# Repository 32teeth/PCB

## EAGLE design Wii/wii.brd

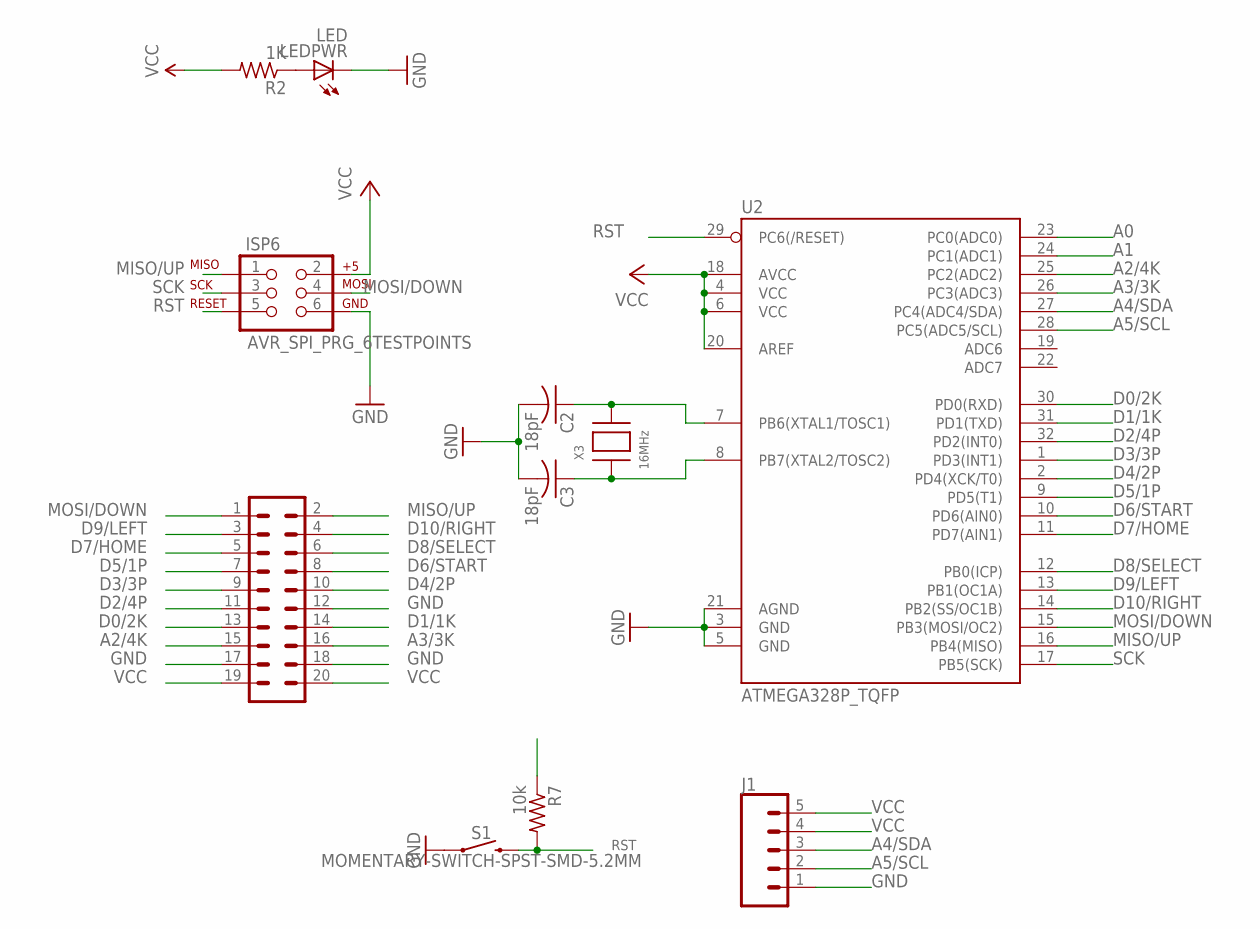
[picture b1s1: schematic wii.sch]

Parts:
C2, C3: 18pF; C0805
ISP6: AVR_SPI_PRG_6TESTPOINTS; 2X3_TEST_POINTS
J1: CONN_05; 1X05
LEDPWR: LED; CHIPLED_0805
R2: 1K; R0805
R7: 10k; R0805
S1: MOMENTARY-SWITCH-SPST-SMD-5.2MM; TACTILE_SWITCH_SMD_5.2MM
U2: ATMEGA328P_TQFP; TQFP32-08
U$1: 20 pin breakout; 2X10_ROUND_NOSILK
X3: 16MHz; NX5032

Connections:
A0: U2.23 (PC0(ADC0))
A1: U2.24 (PC1(ADC1))
A2/4K: U2.25 (PC2(ADC2)), U$1.15
A3/3K: U2.26 (PC3(ADC3)), U$1.16
A4/SDA: J1.3, U2.27 (PC4(ADC4/SDA))
A5/SCL: J1.2, U2.28 (PC5(ADC5/SCL))
D0/2K: U2.30 (PD0(RXD)), U$1.13
D1/1K: U2.31 (PD1(TXD)), U$1.14
D2/4P: U2.32 (PD2(INT0)), U$1.11
D3/3P: U2.1 (PD3(INT1)), U$1.9
D4/2P: U2.2 (PD4(XCK/T0)), U$1.10
D5/1P: U2.9 (PD5(T1)), U$1.7
D6/START: U2.10 (PD6(AIN0)), U$1.8
D7/HOME: U2.11 (PD7(AIN1)), U$1.5
D8/SELECT: U2.12 (PB0(ICP)), U$1.6
D9/LEFT: U2.13 (PB1(OC1A)), U$1.3
D10/RIGHT: U2.14 (PB2(SS/OC1B)), U$1.4
GND: C2.2, C3.2, ISP6.6, J1.1, LEDPWR.C, S1.1, U2.3 (GND), U2.5 (GND), U2.21 (AGND), U$1.12, U$1.17, U$1.18
MISO/UP: ISP6.1, U2.16 (PB4(MISO)), U$1.2
MOSI/DOWN: ISP6.4, U2.15 (PB3(MOSI/OC2)), U$1.1
unnamed: LEDPWR.A, R2.1
unnamed: C2.1, U2.7 (PB6(XTAL1/TOSC1)), X3.P$2
unnamed: C3.1, U2.8 (PB7(XTAL2/TOSC2)), X3.P$1
RST: ISP6.5, R7.2, S1.3 (2), U2.29 (PC6(/RESET))
SCK: ISP6.3, U2.17 (PB5(SCK))
VCC: ISP6.2, J1.4, J1.5, R2.2, R7.1, U2.4 (VCC), U2.6 (VCC), U2.18 (AVCC), U2.20 (AREF), U$1.19, U$1.20

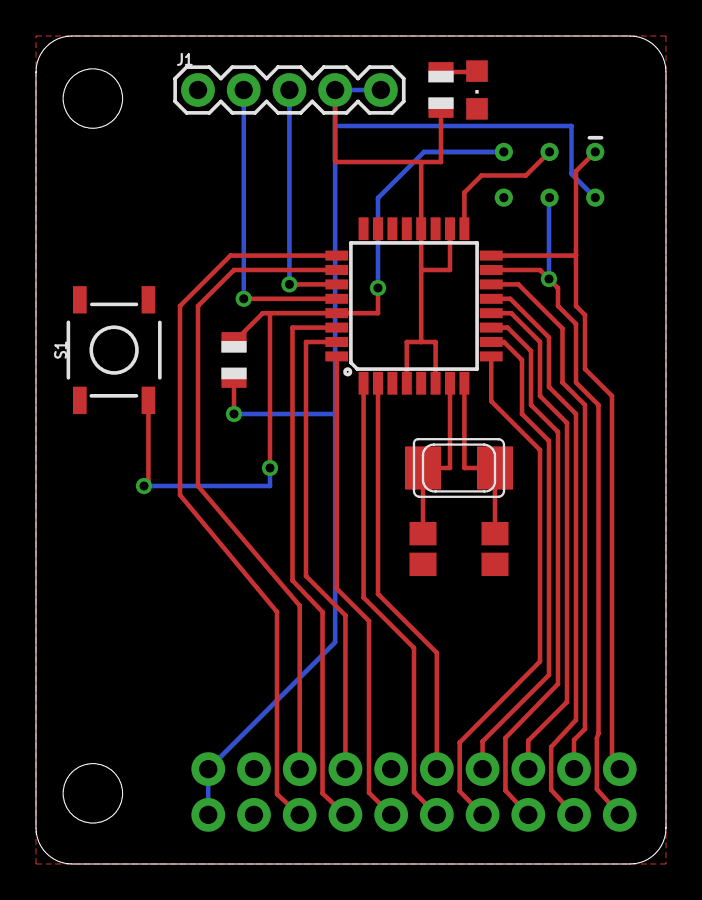
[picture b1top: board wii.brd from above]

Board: 2 copper layers, 35.0 x 46.0 mm, 13 parts (1 on the bottom side), 24 nets.

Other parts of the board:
U$2, U$3: STAND-OFF

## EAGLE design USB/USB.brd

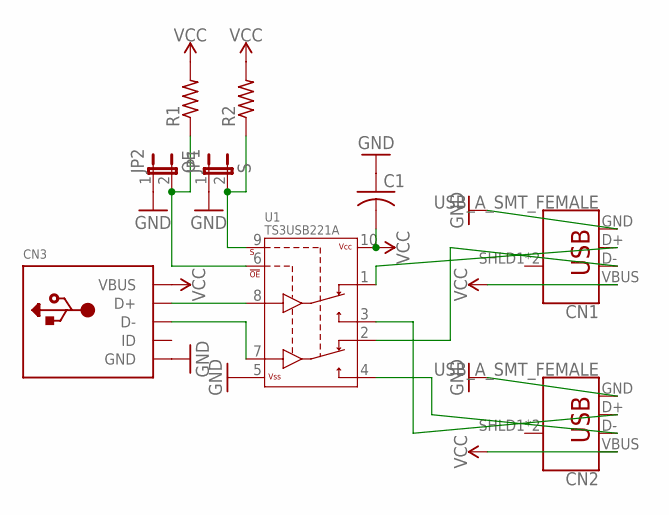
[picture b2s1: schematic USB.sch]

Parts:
C1: C-USC0402K; C0402K
CN1, CN2: USB_A_SMT_FEMALE; USB-A-S-SILK-FEMALE
CN3: USBMINIB; USB-MINIB
JP1: S; 1X02
JP2: OE; 1X02
R1, R2: R-US_R0402; R0402
U1: TS3USB221A; QFN-10-RSE

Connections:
GND: C1.1, CN1.GND, CN2.GND, CN3.GND, JP1.1, JP2.1, U1.5 (VSS)
unnamed: CN3.D+, U1.8 (D+)
unnamed: CN3.D-, U1.7 (D-)
unnamed: CN1.D+, U1.1 (1D+)
unnamed: CN2.D+, U1.3 (2D+)
unnamed: CN1.D-, U1.2 (1D-)
unnamed: CN2.D-, U1.4 (2D-)
unnamed: JP2.2, R1.1, U1.6 (!OE)
unnamed: JP1.2, R2.1, U1.9 (S)
VCC: C1.2, CN1.VBUS, CN2.VBUS, CN3.VBUS, R1.2, R2.2, U1.10 (VCC)

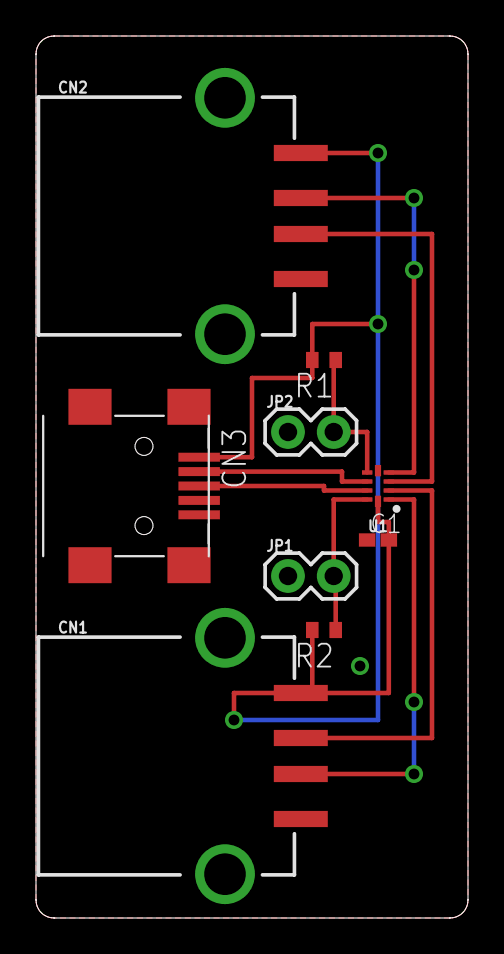
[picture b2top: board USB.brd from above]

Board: 2 copper layers, 24.0 x 49.0 mm, 9 parts (0 on the bottom side), 10 nets.

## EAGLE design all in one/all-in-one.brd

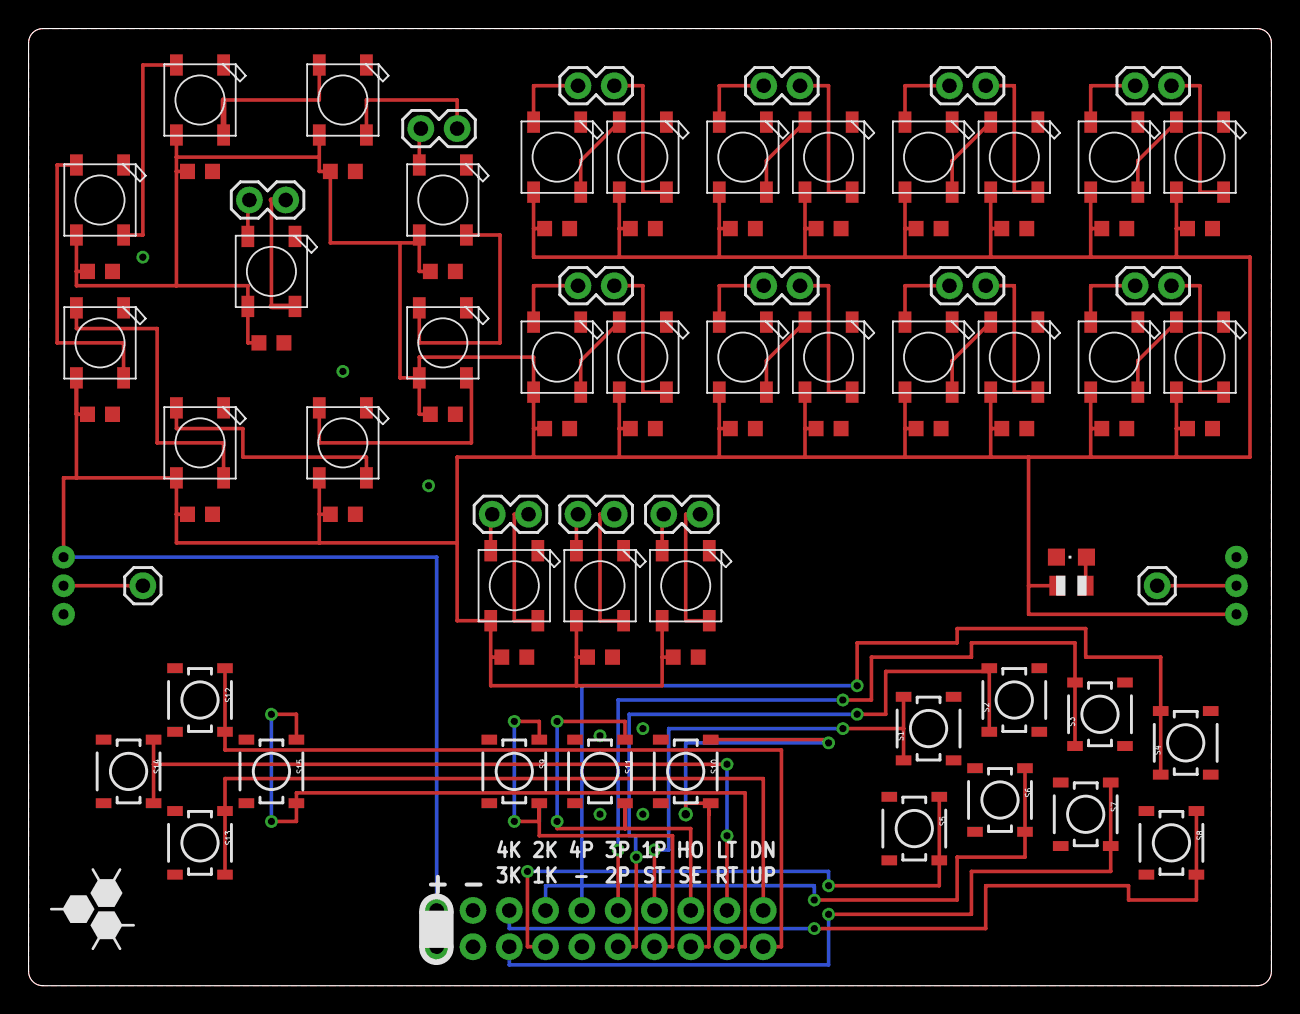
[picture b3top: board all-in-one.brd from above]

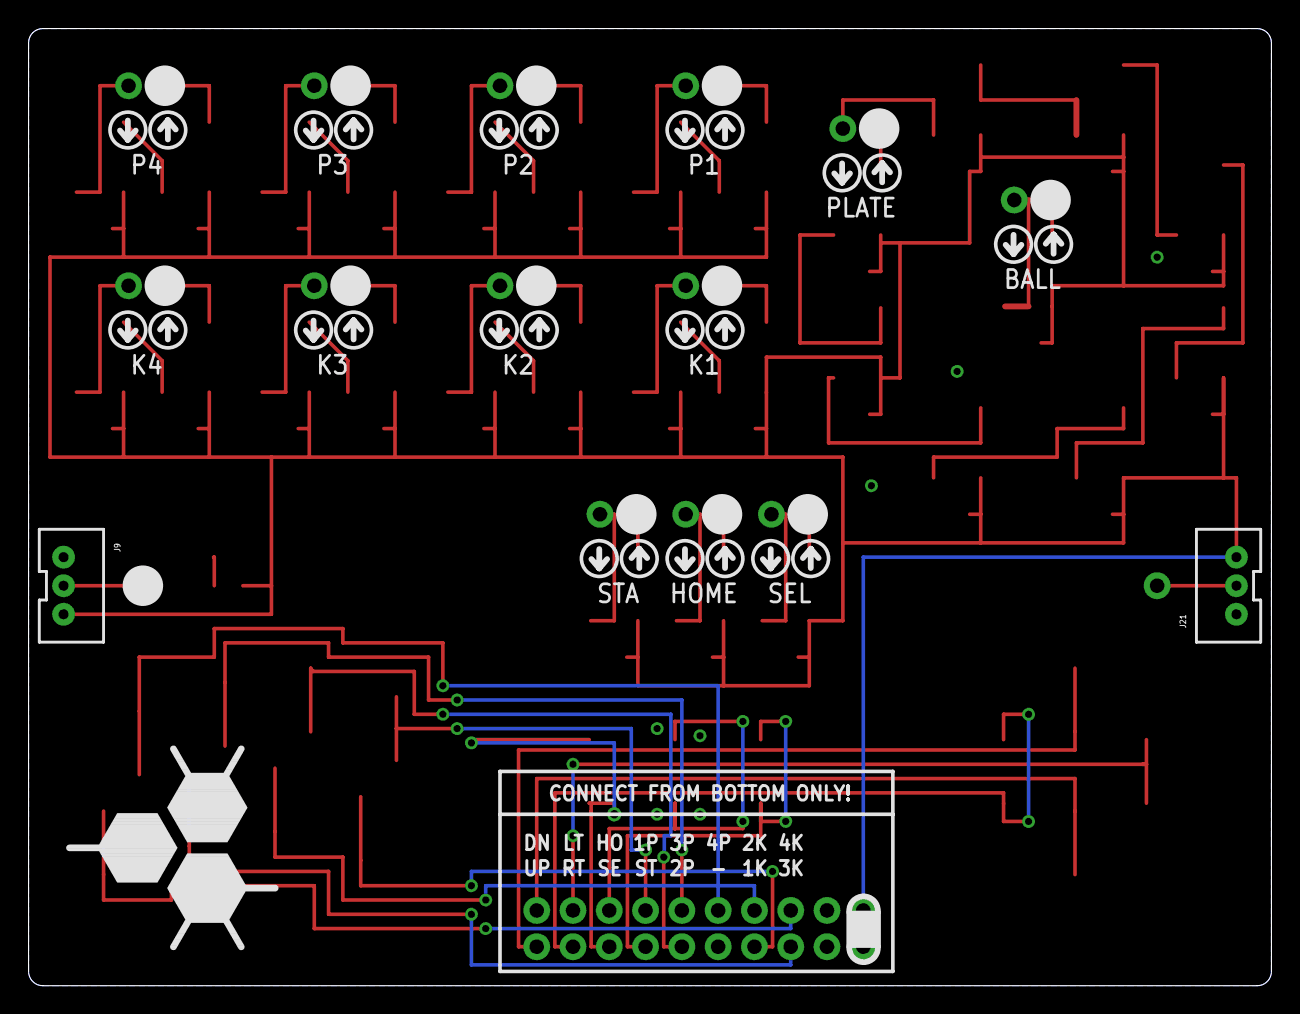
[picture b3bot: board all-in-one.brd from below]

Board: 2 copper layers, 87.0 x 67.0 mm, 91 parts (2 on the bottom side), 61 nets.

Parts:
C1, C2, C3, C4, C5, C6, C7, C8, C9, C10, C11, C12, C13, C14, C15, C16, C17, C18, C19, C20, C21, C22, C23, C24, C25, C26, C27, C28: 0.1uf; C0603K
J1: K1; 1X02
J2: P1; 1X02
J3: K2; 1X02
J4: P2; 1X02
J5: K3; 1X02
J6: P3; 1X02
J7: K4; 1X02
J8: P4; 1X02
J9, J21: led; JST-3-PTH-VERT
J10: DIN; 1X01
J11: START; 1X02
J12: SELECT; 1X02
J13: HOME; 1X02
J14: BALLTOP; 1X02
J15: PLATE; 1X02
J20: DOUT; 1X01
L1, L2, L3, L4, L5, L6, L7, L8, L9, L10, L11, L12, L13, L14, L15, L16, L17, L18, L19, L20, L21, L22, L23, L24, L25, L26, L27, L28: WS2812B
LED1: CHIPLED_0805
R1: R0805
S1: P1; TACTILE_SWITCH_SMD_4.5MM
S2: P2; TACTILE_SWITCH_SMD_4.5MM
S3: P3; TACTILE_SWITCH_SMD_4.5MM
S4: P4; TACTILE_SWITCH_SMD_4.5MM
S5: K1; TACTILE_SWITCH_SMD_4.5MM
S6: K2; TACTILE_SWITCH_SMD_4.5MM
S7: K3; TACTILE_SWITCH_SMD_4.5MM
S8: K4; TACTILE_SWITCH_SMD_4.5MM
S9: START; TACTILE_SWITCH_SMD_4.5MM
S10: SELECT; TACTILE_SWITCH_SMD_4.5MM
S11: HOME; TACTILE_SWITCH_SMD_4.5MM
S12: UP; TACTILE_SWITCH_SMD_4.5MM
S13: DOWN; TACTILE_SWITCH_SMD_4.5MM
S14: LEFT; TACTILE_SWITCH_SMD_4.5MM
S15: RIGHT; TACTILE_SWITCH_SMD_4.5MM
U$1: 20 pin breakout; 2X10_ROUND_NOSILK

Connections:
1K: S5.1, S5.4, U$1.14
1P: S1.1, S1.4, U$1.7
2K: S6.1, S6.4, U$1.13
2P: S2.1, S2.4, U$1.10
3K: S7.1, S7.4, U$1.16
3P: S3.1, S3.4, U$1.9
4K: S8.1, S8.4, U$1.15
4P: S4.1, S4.4, U$1.11
DOWN: S13.1, S13.4, U$1.1
GND: C1.2, C2.2, C3.2, C4.2, C5.2, C6.2, C7.2, C8.2, C9.2, C10.2, C11.2, C12.2, C13.2, C14.2, C15.2, C16.2, C17.2, C18.2, C19.2, C20.2, C21.2, C22.2, C23.2, C24.2, C25.2, C26.2, C27.2, C28.2, J9.1, J21.1, L1.3-GND, L2.3-GND, L3.3-GND, L4.3-GND, L5.3-GND, L6.3-GND, L7.3-GND, L8.3-GND, L9.3-GND, L10.3-GND, L11.3-GND, L12.3-GND, L13.3-GND, L14.3-GND, L15.3-GND, L16.3-GND, L17.3-GND, L18.3-GND, L19.3-GND, L20.3-GND, L21.3-GND, L22.3-GND, L23.3-GND, L24.3-GND, L25.3-GND, L26.3-GND, L27.3-GND, L28.3-GND, LED1.C, S1.2, S1.3, S2.2, S2.3, S3.2, S3.3, S4.2, S4.3, S5.2, S5.3, S6.2, S6.3, S7.2, S7.3, S8.2, S8.3, S9.2, S9.3, S10.2, S10.3, S11.2, S11.3, S12.2, S12.3, S13.2, S13.3, S14.2, S14.3, S15.2, S15.3, U$1.12, U$1.17, U$1.18
HOME: S11.1, S11.4, U$1.5
LEFT: S14.1, S14.4, U$1.3
unnamed: J1.2, L1.4-DIN
unnamed: J1.1, L2.2-DOUT
unnamed: L1.2-DOUT, L2.4-DIN
unnamed: J20.1, J21.2
unnamed: J2.2, L3.4-DIN
unnamed: J2.1, L4.2-DOUT
unnamed: J3.2, L5.4-DIN
unnamed: L5.2-DOUT, L6.4-DIN
unnamed: J3.1, L6.2-DOUT
unnamed: J4.2, L7.4-DIN
unnamed: J4.1, L8.2-DOUT
unnamed: J5.2, L9.4-DIN
unnamed: J5.1, L10.2-DOUT
unnamed: J6.2, L11.4-DIN
unnamed: J6.1, L12.2-DOUT
unnamed: J7.2, L13.4-DIN
unnamed: J7.1, L14.2-DOUT
unnamed: L9.2-DOUT, L10.4-DIN
unnamed: L11.2-DOUT, L12.4-DIN
unnamed: L13.2-DOUT, L14.4-DIN
unnamed: L15.2-DOUT, L16.4-DIN
unnamed: L7.2-DOUT, L8.4-DIN
unnamed: L3.2-DOUT, L4.4-DIN
unnamed: J8.2, L15.4-DIN
unnamed: J8.1, L16.2-DOUT
unnamed: J11.1, L17.2-DOUT
unnamed: J9.2, J10.1
unnamed: J11.2, L17.4-DIN
unnamed: J12.2, L18.4-DIN
unnamed: J12.1, L18.2-DOUT
unnamed: J13.2, L19.4-DIN
unnamed: J13.1, L19.2-DOUT
unnamed: J14.2, L20.4-DIN
unnamed: J14.1, L20.2-DOUT
unnamed: J15.2, L21.4-DIN
unnamed: J15.1, L28.2-DOUT
unnamed: LED1.A, R1.2
unnamed: L27.2-DOUT, L28.4-DIN
unnamed: L26.2-DOUT, L27.4-DIN
unnamed: L25.2-DOUT, L26.4-DIN
unnamed: L24.2-DOUT, L25.4-DIN
unnamed: L23.2-DOUT, L24.4-DIN
unnamed: L22.2-DOUT, L23.4-DIN
unnamed: L21.2-DOUT, L22.4-DIN
RIGHT: S15.1, S15.4, U$1.4
SELECT: S10.1, S10.4, U$1.6
START: S9.1, S9.4, U$1.8
UP: S12.1, S12.4, U$1.2
VCC: C1.1, C2.1, C3.1, C4.1, C5.1, C6.1, C7.1, C8.1, C9.1, C10.1, C11.1, C12.1, C13.1, C14.1, C15.1, C16.1, C17.1, C18.1, C19.1, C20.1, C21.1, C22.1, C23.1, C24.1, C25.1, C26.1, C27.1, C28.1, J9.3, J21.3, L1.1-VDD, L2.1-VDD, L3.1-VDD, L4.1-VDD, L5.1-VDD, L6.1-VDD, L7.1-VDD, L8.1-VDD, L9.1-VDD, L10.1-VDD, L11.1-VDD, L12.1-VDD, L13.1-VDD, L14.1-VDD, L15.1-VDD, L16.1-VDD, L17.1-VDD, L18.1-VDD, L19.1-VDD, L20.1-VDD, L21.1-VDD, L22.1-VDD, L23.1-VDD, L24.1-VDD, L25.1-VDD, L26.1-VDD, L27.1-VDD, L28.1-VDD, R1.1, U$1.19, U$1.20

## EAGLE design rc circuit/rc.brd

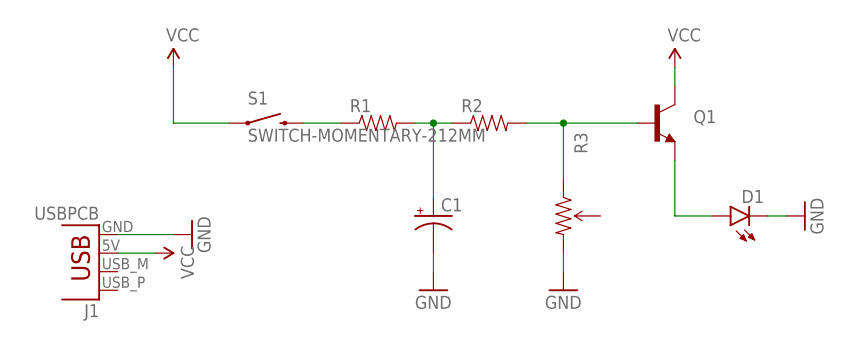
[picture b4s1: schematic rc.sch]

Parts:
C1: CAP_POLPTH1; CPOL-RADIAL-100UF-25V
D1: LED5MM
J1: USBPCB; USB-A-PCB
Q1: TRANSISTOR_NPNP2N2222A; TO-92
R1, R2: RESISTORPTH-1/6W; 1/6W-RES
R3: TRIMPOTPTH; TRIM_POT_PTH
S1: SWITCH-MOMENTARY-212MM; TACTILE-PTH-12MM

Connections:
GND: C1.2 (-), D1.K (C), J1.GND, R3.3 (CW)
unnamed: D1.A, Q1.3 (E)
unnamed: Q1.2 (B), R2.2, R3.1 (CCW)
unnamed: C1.1 (+), R1.2, R2.1
unnamed: R1.1, S1.3 (2)
VCC: J1.5V (VBUS), Q1.1 (C), S1.1

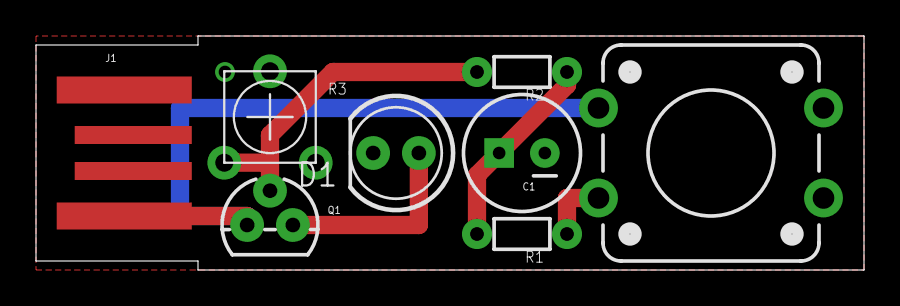
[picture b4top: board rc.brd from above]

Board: 2 copper layers, 46.0 x 13.0 mm, 8 parts (0 on the bottom side), 6 nets.

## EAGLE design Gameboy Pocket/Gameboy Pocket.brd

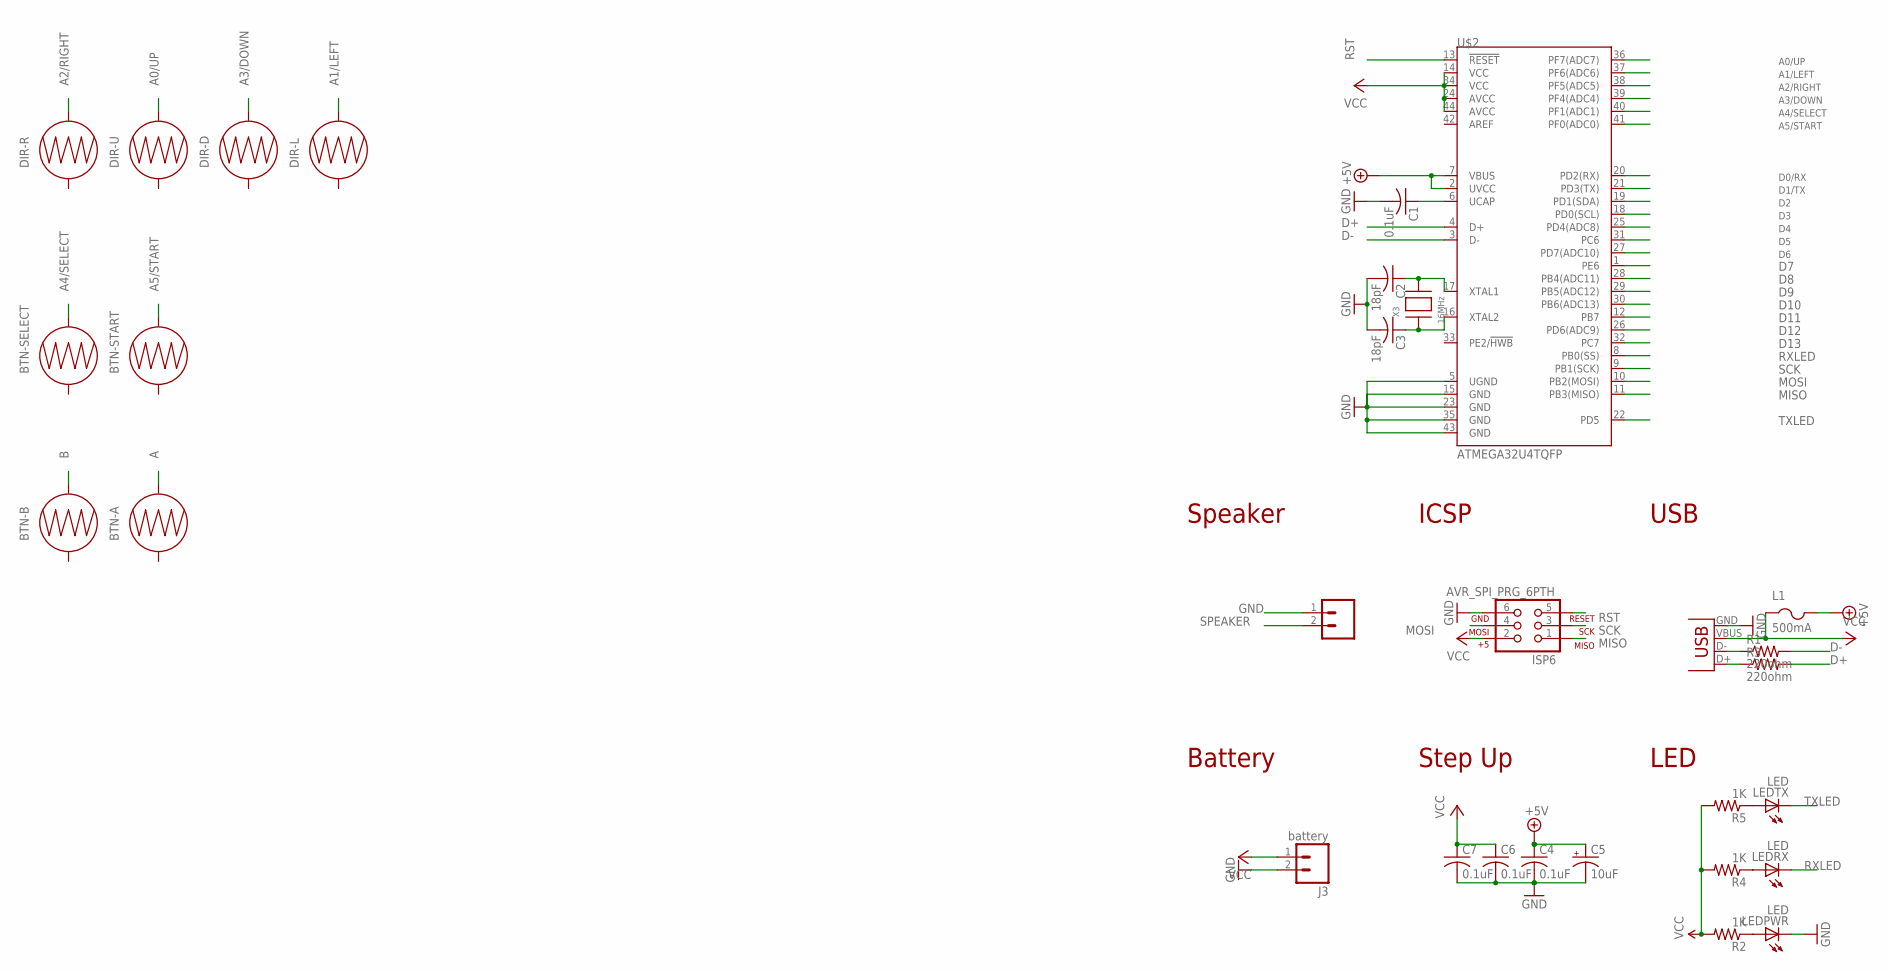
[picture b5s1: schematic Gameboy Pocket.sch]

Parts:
BTN-A: BUTTON-CONDUCTIVESMD; BUTTON-CONDUCTIVE
BTN-B: BUTTON-CONDUCTIVESMD; BUTTON-CONDUCTIVE
BTN-SELECT: BUTTON-CONDUCTIVESMD; BUTTON-CONDUCTIVE
BTN-START: BUTTON-CONDUCTIVESMD; BUTTON-CONDUCTIVE
C1, C4, C6, C7: 0.1uF; C0805
C2, C3: 18pF; C0805
C5: 10uF; EIA3216
CN1: USB-SMD-NS; USB-MINIB-NOSTOP
DIR-D: BUTTON-CONDUCTIVESMD; BUTTON-CONDUCTIVE
DIR-L: BUTTON-CONDUCTIVESMD; BUTTON-CONDUCTIVE
DIR-R: BUTTON-CONDUCTIVESMD; BUTTON-CONDUCTIVE
DIR-U: BUTTON-CONDUCTIVESMD; BUTTON-CONDUCTIVE
ISP6: AVR_SPI_PRG_6PTH; 2X3
J3: battery; JST-2-PTH-VERT
JP2: M02PTH; 1X02
L1: 500mA; R1206
LEDPWR: LED; CHIPLED_0805
LEDRX: LED; CHIPLED_0805
LEDTX: LED; CHIPLED_0805
R1, R3: 220ohm; R0805
R2, R4, R5: 1K; R0805
U$2: ATMEGA32U4TQFP; SPARKFUN-DIGITALIC_TQFP44
X3: 16MHz; NX5032

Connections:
+5V: C4.1, C5.A (+), L1.2, U$2.2 (UVCC), U$2.7 (VBUS)
A: BTN-A.2
A0/UP: DIR-U.2, U$2.36 (PF7(ADC7))
A1/LEFT: DIR-L.2, U$2.37 (PF6(ADC6))
A2/RIGHT: DIR-R.2, U$2.38 (PF5(ADC5))
A3/DOWN: DIR-D.2, U$2.39 (PF4(ADC4))
A4/SELECT: BTN-SELECT.2, U$2.40 (PF1(ADC1))
A5/START: BTN-START.2, U$2.41 (PF0(ADC0))
B: BTN-B.2
D0/RX: U$2.20 (PD2(RX))
D1/TX: U$2.21 (PD3(TX))
D2: U$2.19 (PD1(SDA))
D3: U$2.18 (PD0(SCL))
D4: U$2.25 (PD4(ADC8))
D5: U$2.31 (PC6)
D6: U$2.27 (PD7(ADC10))
D7: U$2.1 (PE6)
D8: U$2.28 (PB4(ADC11))
D9: U$2.29 (PB5(ADC12))
D10: U$2.30 (PB6(ADC13))
D11: U$2.12 (PB7)
D12: U$2.26 (PD6(ADC9))
D13: U$2.32 (PC7)
D+: R3.2, U$2.4 (D+)
D-: R1.2, U$2.3 (D-)
GND: C1.2, C2.2, C3.2, C4.2, C5.C (-), C6.2, C7.2, CN1.GND, ISP6.6, J3.2, JP2.1, LEDPWR.C, U$2.5 (UGND), U$2.15 (GND), U$2.23 (GND), U$2.35 (GND), U$2.43 (GND)
MISO: ISP6.1, U$2.11 (PB3(MISO))
MOSI: ISP6.4, U$2.10 (PB2(MOSI))
unnamed: LEDPWR.A, R2.1
unnamed: CN1.D+, R3.1
unnamed: CN1.D-, R1.1
unnamed: LEDRX.A, R4.1
unnamed: LEDTX.A, R5.1
unnamed: C2.1, U$2.17 (XTAL1), X3.P$2
unnamed: C3.1, U$2.16 (XTAL2), X3.P$1
RST: ISP6.5, U$2.13 (!RESET)
RXLED: LEDRX.C, U$2.8 (PB0(SS))
SCK: ISP6.3, U$2.9 (PB1(SCK))
SPEAKER: JP2.2
TXLED: LEDTX.C, U$2.22 (PD5)
UCAP: C1.1, U$2.6 (UCAP)
VCC: C6.1, C7.1, CN1.VBUS, ISP6.2, J3.1, L1.1, R2.2, R4.2, R5.2, U$2.14 (VCC), U$2.24 (AVCC), U$2.34 (VCC), U$2.44 (AVCC)

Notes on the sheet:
Speaker
ICSP
USB
LED
Step Up
Battery

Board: 2 copper layers, 40 parts (0 on the bottom side), 25 nets, no tracks yet.

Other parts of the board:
U$3, U$4, U$5, U$6, U$7, U$8, U$9, U$10, U$11, U$12: STAND-OFF

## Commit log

2017-02-14 added sega and all in one
2017-02-14 updated all in one
2017-02-15 rooby dooby dooby
2017-03-06 Mon Mar 6 17:43:38 EST 2017
2017-03-07 Tue Mar 7 09:28:05 EST 2017
2017-03-10 Fri Mar 10 05:58:47 EST 2017
2017-03-13 Mon Mar 13 10:29:26 EDT 2017
2017-03-13 Mon Mar 13 19:17:02 EDT 2017
2017-03-14 Tue Mar 14 06:59:41 EDT 2017
2017-03-15 Wed Mar 15 19:26:25 EDT 2017

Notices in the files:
parts and their libraries:
SparkFun-Connectors: Licensing: CC v3.0 Share-Alike You are welcome to use this library for commercial purposes.
SparkFun-Retired: Licensing:Creative Commons ShareAlike 4.0 International - https://creativecommons.org/licenses/by-sa/4.0
